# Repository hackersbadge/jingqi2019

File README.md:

# Hacker's Badge for JD's JingQi 2019, Beijing

- [x] Hardware: WhiteA10n3
- [x] Code: chenhuitao/xwings

* SoC: MTK7688
* 1 x Antenna 
* WiFi Capable
* Breed Bootloader
* 2 Buttons
* 3 x LED

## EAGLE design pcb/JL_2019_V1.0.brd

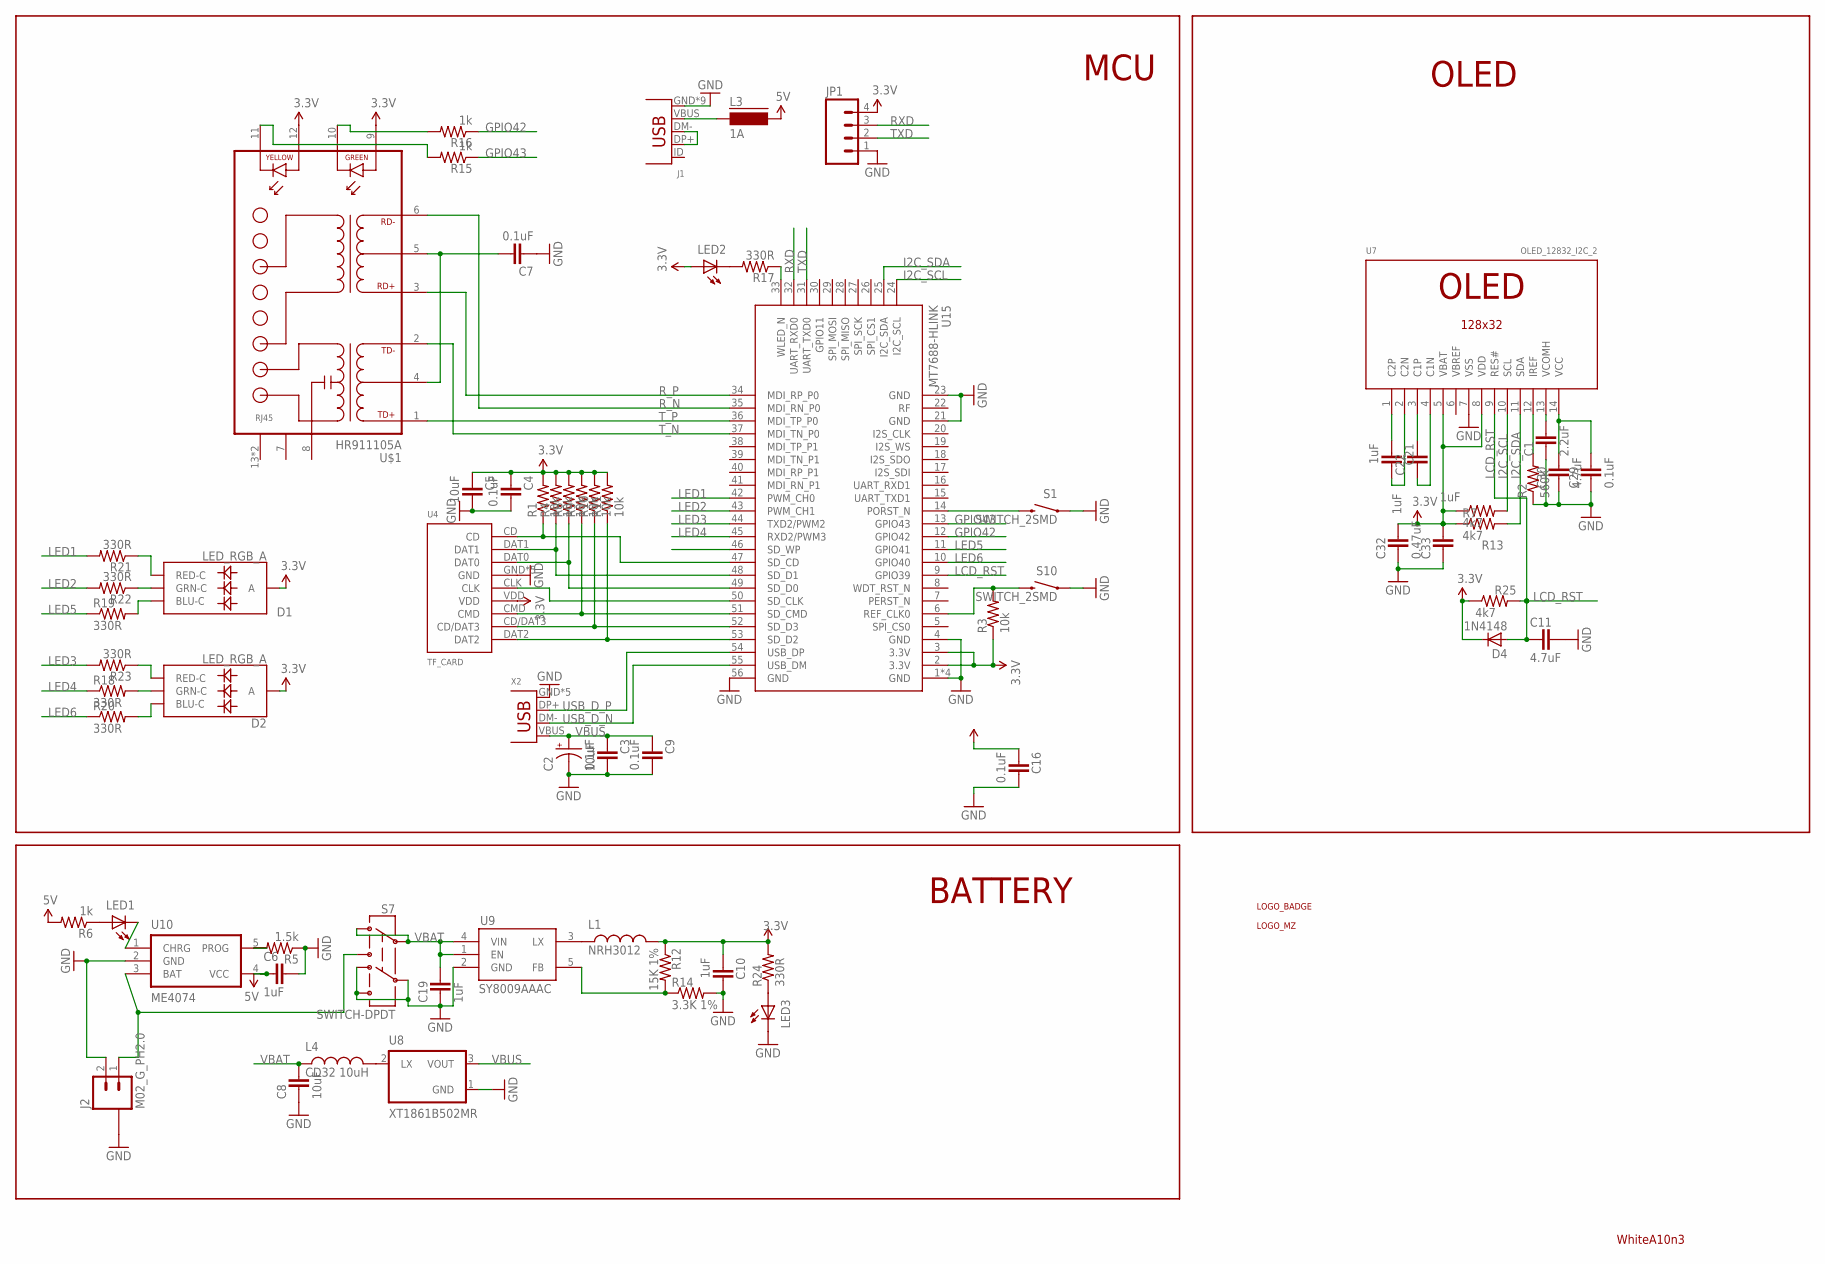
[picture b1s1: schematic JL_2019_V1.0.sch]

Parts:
C1: 2.2uF; 0603-CAP
C2: 10uF; EIA3216
C3, C4, C7, C9, C16, C29: 0.1uF; 0603-CAP
C5, C8: 10uF; 0603-CAP
C6, C10, C19, C21, C22, C33: 1uF; 0603-CAP
C11, C30: 4.7uF; 0603-CAP
C32: 0.47uF; 0603-CAP
D1, D2: LED_RGB_A; RGB-1615-A
D4: 1N4148; SOD-323F
J1: USB_5_MICRO_4; USB-MICRO-4
J2: M02_G_PH2.0; PH2.0_SMD_2
JP1: M04PTH; 1X04
L1: NRH3012; 1210
L3: 1A; FB805
L4: CD32 10uH; CD32
LED1, LED2, LED3: LED0603; LED-0603
R1, R3, R4, R8, R9, R10, R11: 10k; 0603-RES
R2: 560K; 0603-RES
R5: 1.5k; 0603-RES
R6, R15, R16: 1k; 0603-RES
R7, R13, R25: 4k7; 0603-RES
R12: 15K 1%; 0603-RES
R14: 3.3K 1%; 0603-RES
R17, R18, R19, R20, R21, R22, R23, R24: 330R; 0603-RES
S1, S10: SWITCH_2SMD; TACTILE_SWITCH_SMD
S7: SWITCH-DPDT; MSS22D18
U4: TF_CARD; MICRO-SD-TF
U5: LOGO_BADGE_24.3_20_S
U6: LOGO_MZ_16_14_S
U7: OLED_12832_I2C_2; OLED_12832_0.91_2
U8: XT1861B502MR; SOT23-3
U9: SY8009AAAC; SOT23-5
U10: ME4074; SOT23-5
U15: MT7688-HLINK; MT7688_HLINK
U$1: HR911105A
X2: USB_4_4; USB-A-4

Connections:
3.3V: C4.2, C5.2, C10.2, C16.2, C32.1, C33.1, D1.A, D2.A, D4.C, JP1.4, L1.2, LED2.A, R1.2, R3.1, R4.2, R7.1, R8.2, R9.2, R10.2, R11.2, R12.1, R13.1, R24.2, R25.1, U4.VDD, U7.5 (VBAT), U7.8 (VDD), U15.2 (3.3V), U15.3 (3.3V), U$1.9, U$1.12
5V: C6.2, L3.1, R6.2, U10.4 (VCC)
GND: C1.2, C2.C (-), C3.1, C4.1, C5.1, C6.1, C7.2, C8.2, C9.1, C10.1, C11.1, C16.1, C19.2, C29.2, C30.2, C32.2, C33.2, J1.GND, J1.MT1 (GND), J1.MT2 (GND), J1.MT5 (GND), J1.MT6 (GND), J1.MT7 (GND), J1.MT8 (GND), J1.MT9 (GND), J1.MT10 (GND), J2.2, J2.G1 (G), J2.G2 (G), JP1.1, LED3.C, R2.1, R5.1, R14.2, S1.1, S7.4, S7.5, S7.6, S10.1, U4.GND, U4.GND1 (GND), U4.GND2 (GND), U4.GND3 (GND), U4.GND4 (GND), U7.7 (VSS), U8.1 (GND), U9.2 (GND), U10.2 (GND), U15.1 (GND), U15.4 (GND), U15.21 (GND), U15.23 (GND), U15.56 (GND), U15.PAD (GND), U15.PAD1 (GND), U15.PAD2 (GND), X2.GND, X2.P$5 (GND), X2.P$6 (GND), X2.P$7 (GND), X2.P$8 (GND)
GPIO42: R16.1, U15.12 (GPIO42)
GPIO43: R15.1, U15.13 (GPIO43)
I2C_SCL: R13.2, U7.10 (SCL), U15.24 (I2C_SCL)
I2C_SDA: R7.2, U7.11 (SDA), U15.25 (I2C_SDA)
LCD_RST: C11.2, D4.A, R25.2, U7.9 (RES#), U15.9 (GPIO39)
LED1: R21.2, U15.42 (PWM_CH0)
LED2: R22.2, U15.43 (PWM_CH1)
LED3: R23.2, U15.44 (TXD2/PWM2)
LED4: R18.1, U15.45 (RXD2/PWM3)
LED5: R19.1, U15.11 (GPIO41)
LED6: R20.1, U15.10 (GPIO40)
unnamed: L4.P$2 (2), U8.2 (LX)
unnamed: LED3.A, R24.1
unnamed: J2.1, S7.3, U10.3 (BAT)
unnamed: C1.1, U7.13 (VCOMH)
unnamed: D1.R (RED-C), R21.1
unnamed: D1.G (GRN-C), R22.1
unnamed: R5.2, U10.5 (PROG)
unnamed: R11.1, U4.DAT2, U15.53 (SD_D2)
unnamed: R10.1, U4.CD/DAT3, U15.52 (SD_D3)
unnamed: LED1.A, R6.1
unnamed: LED1.C, U10.1 (CHRG)
unnamed: J1.VBUS, L3.2
unnamed: R9.1, U4.CMD, U15.51 (SD_CMD)
unnamed: U4.CLK, U15.50 (SD_CLK)
unnamed: R1.1, U4.CD, U15.47 (SD_CD)
unnamed: C21.2, U7.1 (C2P)
unnamed: C21.1, U7.2 (C2N)
unnamed: C22.1, U7.3 (C1P)
unnamed: C22.2, U7.4 (C1N)
unnamed: R8.1, U4.DAT0, U15.49 (SD_D0)
unnamed: C29.1, C30.1, U7.14 (VCC)
unnamed: R2.2, U7.12 (IREF)
unnamed: R4.1, U4.DAT1, U15.48 (SD_D1)
unnamed: L1.1, U9.3 (LX)
unnamed: R12.2, R14.1, U9.5 (FB)
unnamed: D1.B (BLU-C), R19.2
unnamed: D2.R (RED-C), R23.1
unnamed: D2.G (GRN-C), R18.2
unnamed: C7.1, U$1.4, U$1.5
unnamed: R15.2, U$1.11
unnamed: R16.2, U$1.10
unnamed: LED2.C, R17.2
unnamed: R17.1, U15.33 (WLED_N)
unnamed: D2.B (BLU-C), R20.2
unnamed: J1.DM- (D-), J1.DP+ (D+)
RST: S1.3 (2), U15.14 (PORST_N)
RST2: R3.2, S10.3 (2), U15.6 (REF_CLK0)
RXD: JP1.3, U15.32 (UART_RXD0)
R_N: U15.35 (MDI_RN_P0), U$1.6
R_P: U15.34 (MDI_RP_P0), U$1.3
TXD: JP1.2, U15.31 (UART_TXD0)
T_N: U15.37 (MDI_TN_P0), U$1.2
T_P: U15.36 (MDI_TP_P0), U$1.1
USB_D_N: U15.55 (USB_DM), X2.DM-
USB_D_P: U15.54 (USB_DP), X2.DP+
VBAT: C8.1, C19.1, L4.P$1 (1), S7.1, S7.2, U9.1 (EN), U9.4 (VIN)
VBUS: C2.A (+), C3.2, C9.2, U8.3 (VOUT), X2.VBUS

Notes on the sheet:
MCU
BATTERY
WhiteA10n3
OLED

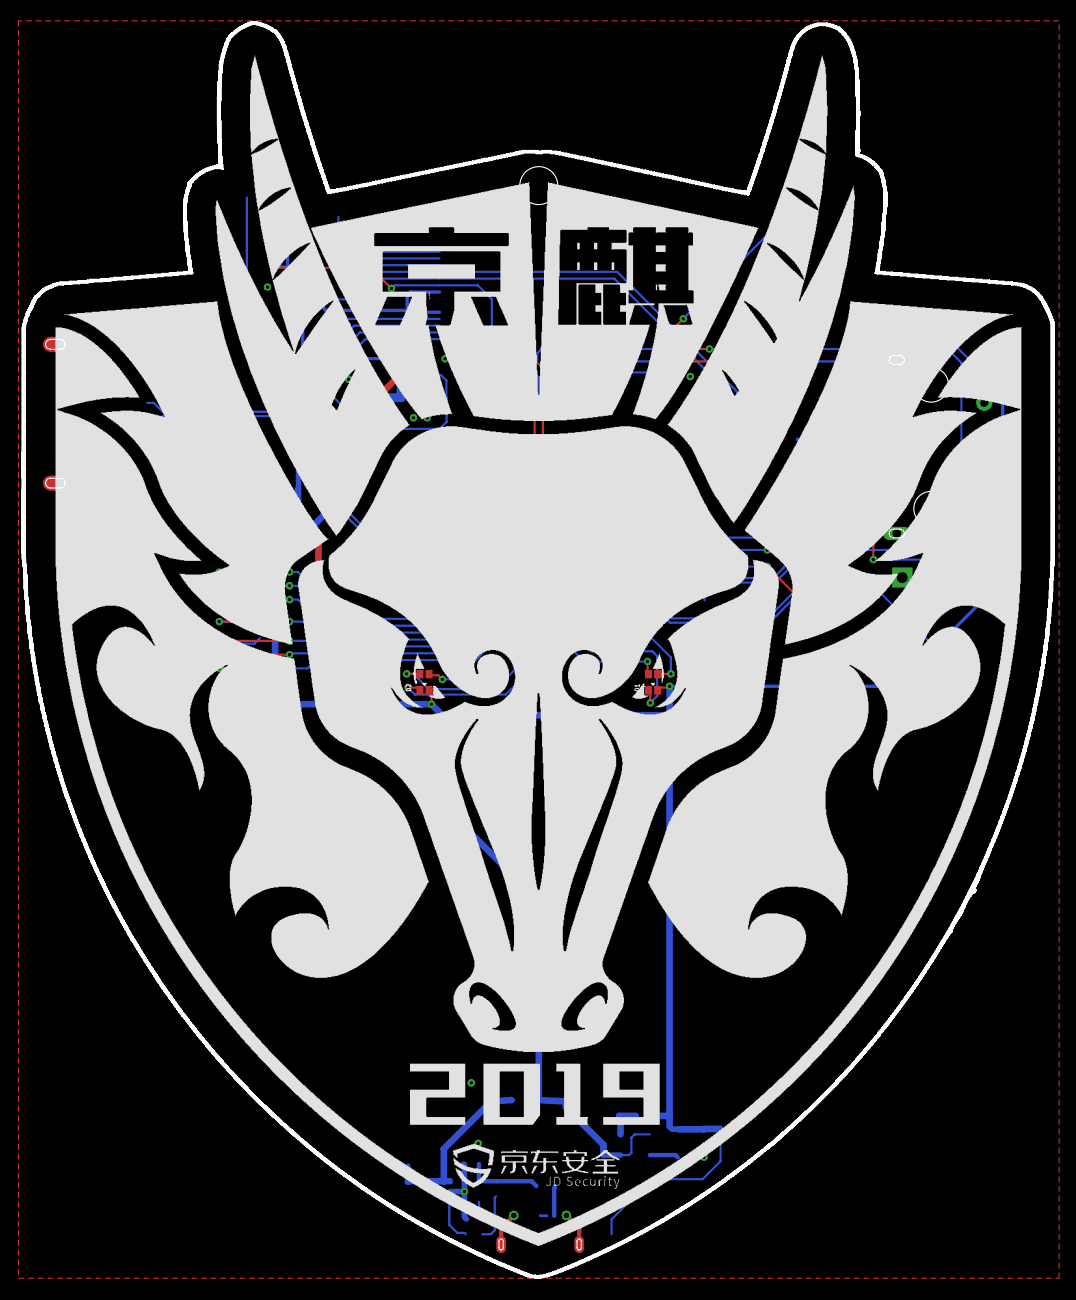
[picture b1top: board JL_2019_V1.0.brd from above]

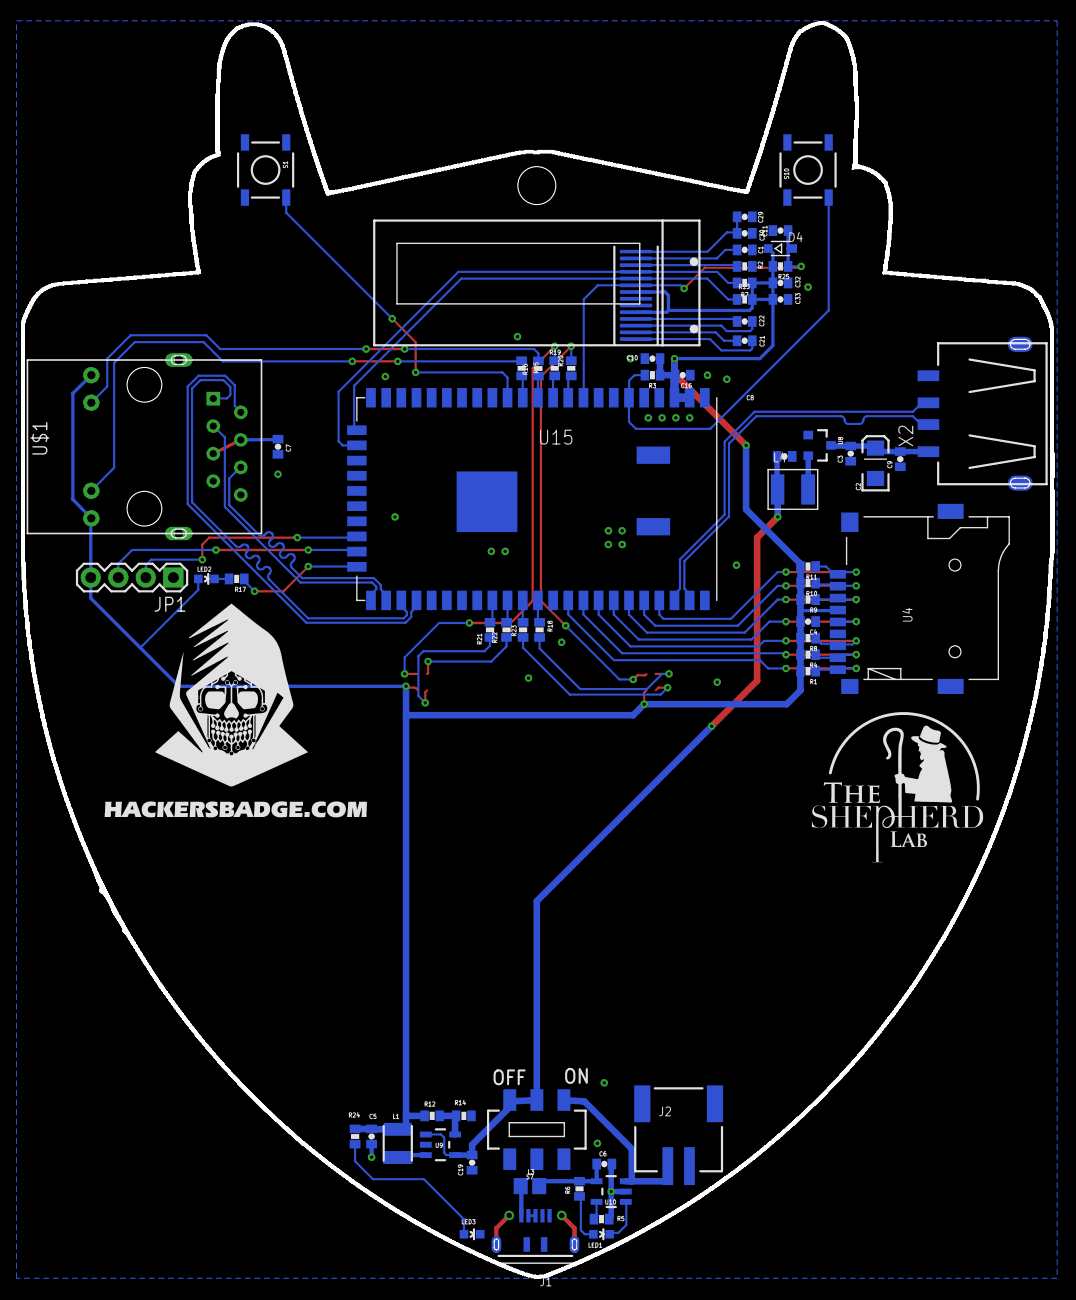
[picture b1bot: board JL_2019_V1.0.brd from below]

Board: 2 copper layers, 95.2 x 115.9 mm, 69 parts (67 on the bottom side), 61 nets.

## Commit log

2019-12-23 pending pcb
2019-12-23 upload pcb
2019-12-29 upload pics

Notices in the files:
parts and their libraries:
2SparkFun: Licensing: CC v3.0 Share-Alike You are welcome to use this library for commercial purposes.
